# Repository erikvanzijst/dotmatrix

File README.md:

16x16 Monochrome Dot Matrix Display
===================================

A project to design and create a custom LED matrix display.

Full writeup and details at: https://medium.com/@erikvanzijst/custom-16x16-matrix-display-pcb-96c40290c8bc

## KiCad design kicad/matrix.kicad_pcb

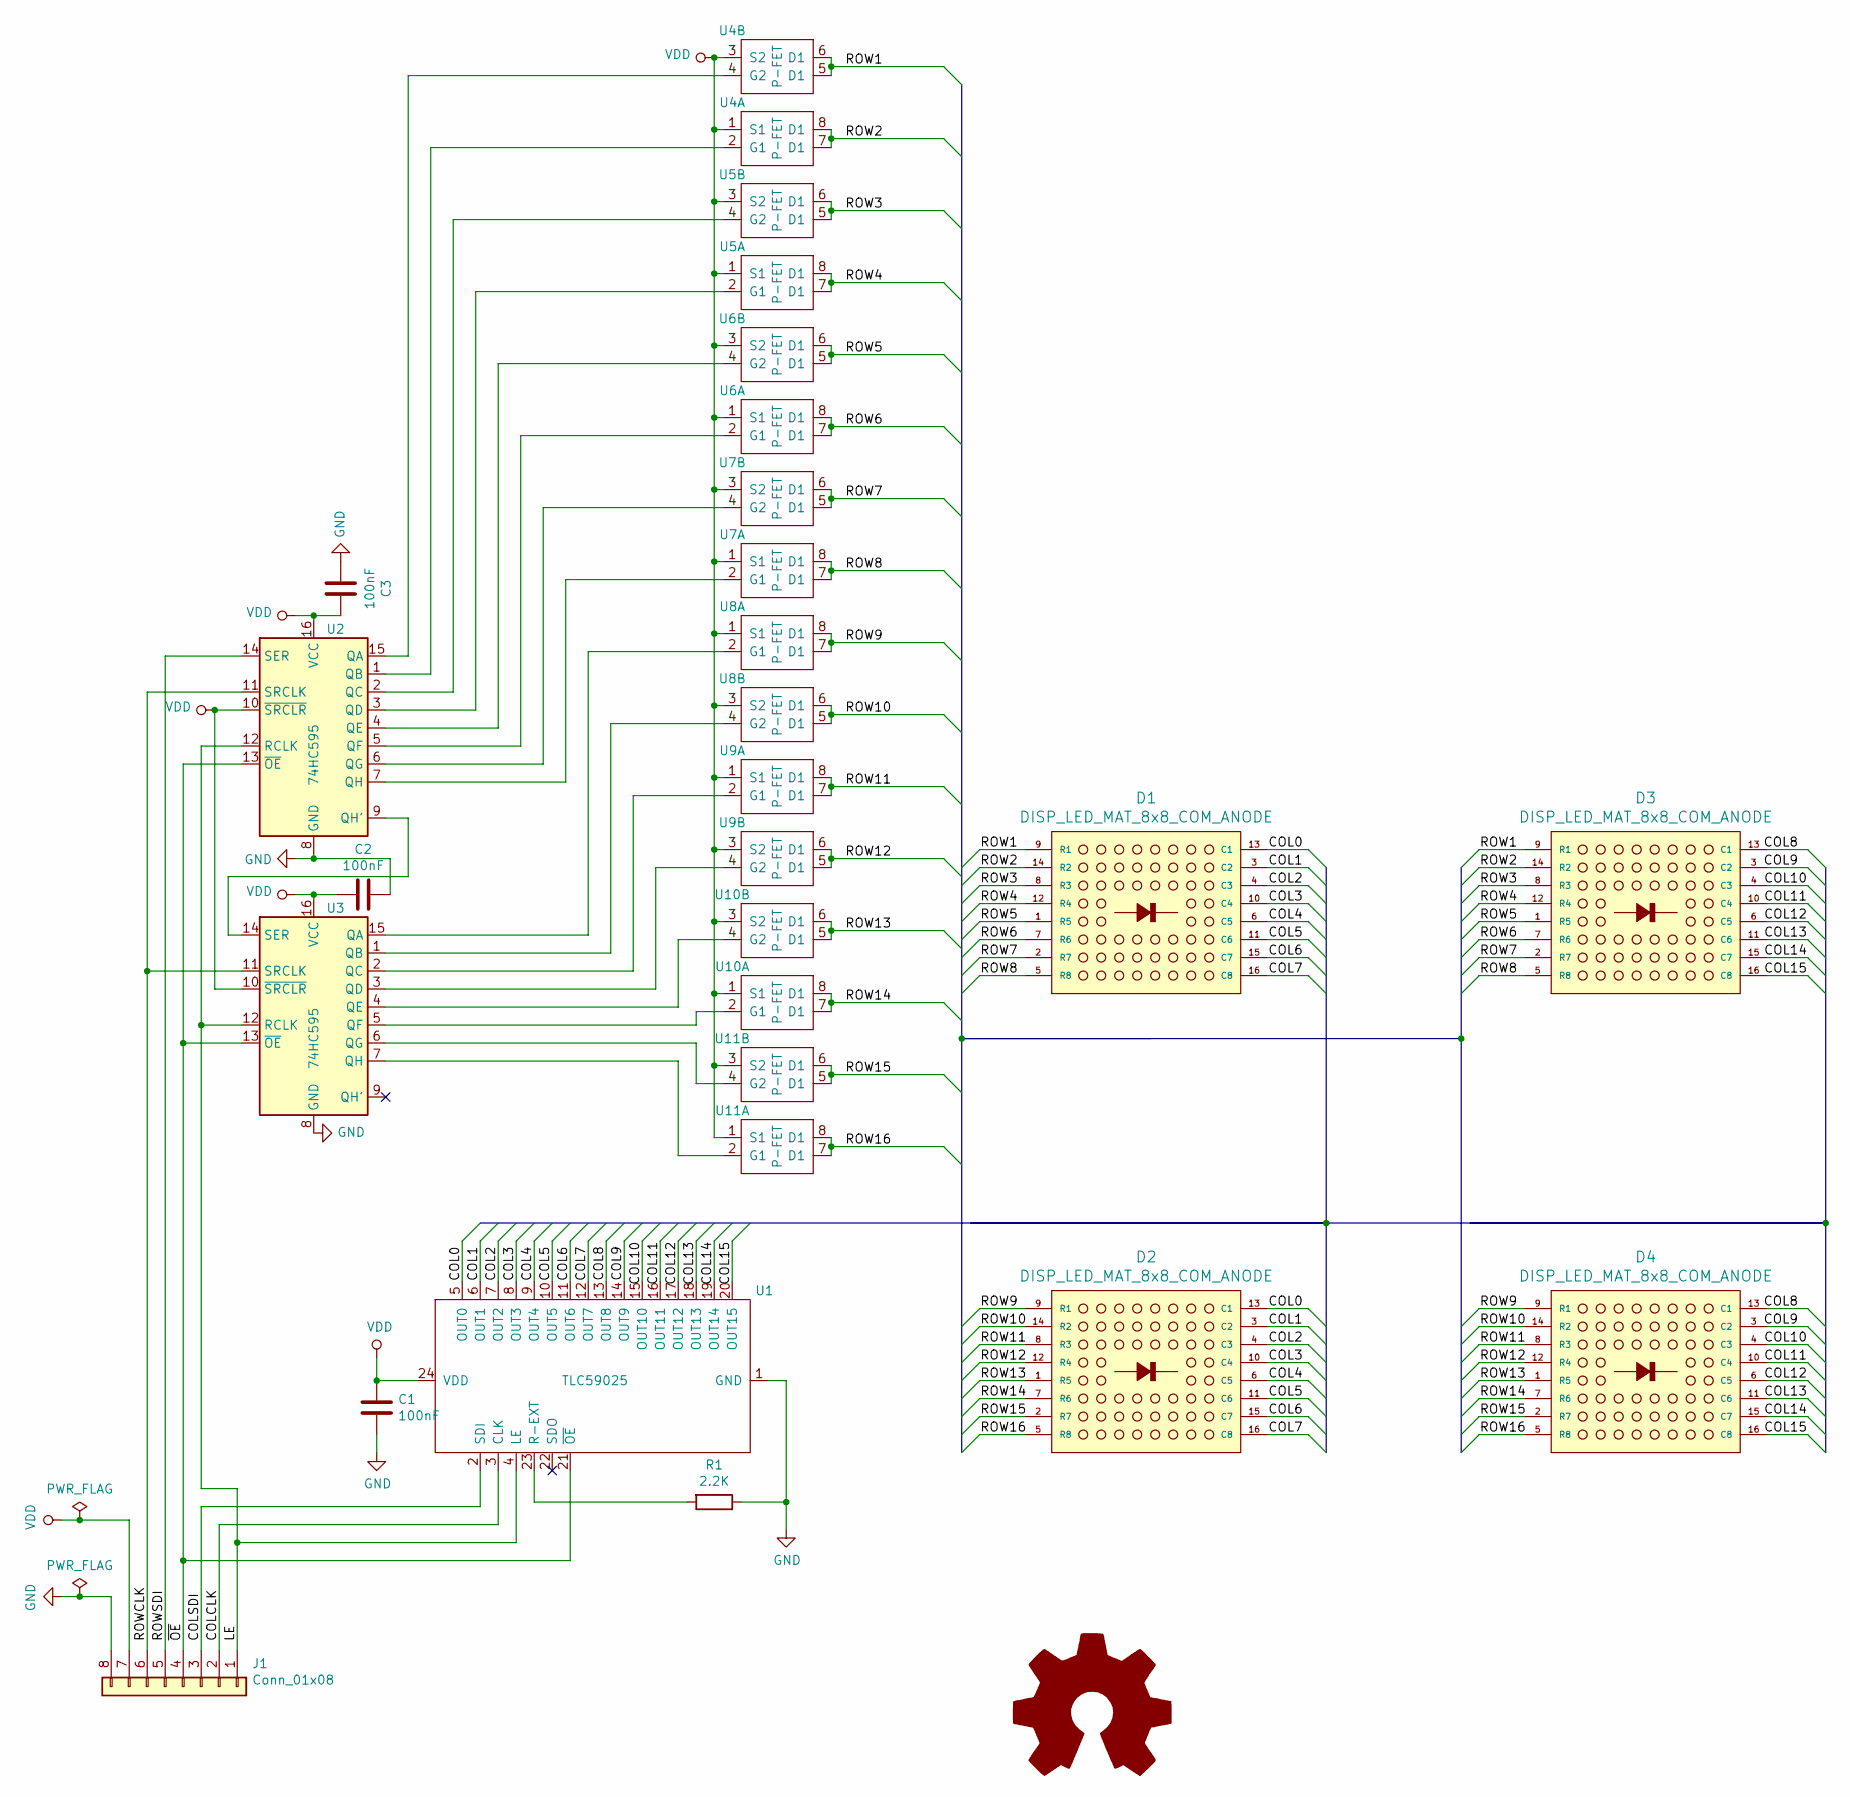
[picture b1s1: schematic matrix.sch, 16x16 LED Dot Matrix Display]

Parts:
C1, C2, C3: 100nF; C_0805_2012Metric_Pad1.15x1.40mm_widepads
D1, D2, D3, D4: DISP_LED_MAT_8x8_COM_ANODE; LED_8x8_3MM_38x38MM
J1: Conn_01x08; PinHeader_1x08_P2.54mm_Horizontal
R1: 2.2K; R_1206_3216Metric_Pad1.42x1.75mm_widepads
U1: TLC59025; SSOP-24_3.9x8.7mm_P0.635mm_widepads
U2, U3: 74HC595; SOIC-16_3.9x9.9mm_P1.27mm_widepads
U4, U5, U6, U7, U8, U9, U10, U11: P-FET; SOIC-8_3.9x4.9mm_P1.27mm_widepads

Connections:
/COL0: D1.13 (C1), D2.13 (C1), U1.5 (OUT0)
/COL1: D1.3 (C2), D2.3 (C2), U1.6 (OUT1)
/COL2: D1.4 (C3), D2.4 (C3), U1.7 (OUT2)
/COL3: D1.10 (C4), D2.10 (C4), U1.8 (OUT3)
/COL4: D1.6 (C5), D2.6 (C5), U1.9 (OUT4)
/COL5: D1.11 (C6), D2.11 (C6), U1.10 (OUT5)
/COL6: D1.15 (C7), D2.15 (C7), U1.11 (OUT6)
/COL7: D1.16 (C8), D2.16 (C8), U1.12 (OUT7)
/COL8: D3.13 (C1), D4.13 (C1), U1.13 (OUT8)
/COL9: D3.3 (C2), D4.3 (C2), U1.14 (OUT9)
/COL10: D3.4 (C3), D4.4 (C3), U1.15 (OUT10)
/COL11: D3.10 (C4), D4.10 (C4), U1.16 (OUT11)
/COL12: D3.6 (C5), D4.6 (C5), U1.17 (OUT12)
/COL13: D3.11 (C6), D4.11 (C6), U1.18 (OUT13)
/COL14: D3.15 (C7), D4.15 (C7), U1.19 (OUT14)
/COL15: D3.16 (C8), D4.16 (C8), U1.20 (OUT15)
/COLCLK: J1.2, U1.3 (CLK)
/COLSDI: J1.3, U1.2 (SDI)
/LE: J1.1, U1.4 (LE), U2.12 (RCLK), U3.12 (RCLK)
/ROW1: D1.9 (R1), D3.9 (R1), U4.5 (D1), U4.6 (D1)
/ROW2: D1.14 (R2), D3.14 (R2), U4.7 (D1), U4.8 (D1)
/ROW3: D1.8 (R3), D3.8 (R3), U5.5 (D1), U5.6 (D1)
/ROW4: D1.12 (R4), D3.12 (R4), U5.7 (D1), U5.8 (D1)
/ROW5: D1.1 (R5), D3.1 (R5), U6.5 (D1), U6.6 (D1)
/ROW6: D1.7 (R6), D3.7 (R6), U6.7 (D1), U6.8 (D1)
/ROW7: D1.2 (R7), D3.2 (R7), U7.5 (D1), U7.6 (D1)
/ROW8: D1.5 (R8), D3.5 (R8), U7.7 (D1), U7.8 (D1)
/ROW9: D2.9 (R1), D4.9 (R1), U8.7 (D1), U8.8 (D1)
/ROW10: D2.14 (R2), D4.14 (R2), U8.5 (D1), U8.6 (D1)
/ROW11: D2.8 (R3), D4.8 (R3), U9.7 (D1), U9.8 (D1)
/ROW12: D2.12 (R4), D4.12 (R4), U9.5 (D1), U9.6 (D1)
/ROW13: D2.1 (R5), D4.1 (R5), U10.5 (D1), U10.6 (D1)
/ROW14: D2.7 (R6), D4.7 (R6), U10.7 (D1), U10.8 (D1)
/ROW15: D2.2 (R7), D4.2 (R7), U11.5 (D1), U11.6 (D1)
/ROW16: D2.5 (R8), D4.5 (R8), U11.7 (D1), U11.8 (D1)
/ROWCLK: J1.6, U2.11 (SRCLK), U3.11 (SRCLK)
/ROWSDI: J1.5, U2.14 (SER)
/~OE: J1.4, U1.21 (~OE), U2.13 (~OE), U3.13 (~OE)
GND: C1.2, C2.1, C3.2, J1.8, R1.1, U1.1 (GND), U2.8 (GND), U3.8 (GND)
unnamed: R1.2, U1.23 (R-EXT)
unnamed: U2.1 (QB), U4.2 (G1)
unnamed: U2.2 (QC), U5.4 (G2)
unnamed: U2.3 (QD), U5.2 (G1)
unnamed: U2.4 (QE), U6.4 (G2)
unnamed: U2.5 (QF), U6.2 (G1)
unnamed: U2.6 (QG), U7.4 (G2)
unnamed: U2.7 (QH), U7.2 (G1)
unnamed: U2.9 (QH'), U3.14 (SER)
unnamed: U2.15 (QA), U4.4 (G2)
unnamed: U3.1 (QB), U8.4 (G2)
unnamed: U3.2 (QC), U9.2 (G1)
unnamed: U3.3 (QD), U9.4 (G2)
unnamed: U3.15 (QA), U8.2 (G1)
unnamed: U3.5 (QF), U10.2 (G1)
unnamed: U3.4 (QE), U10.4 (G2)
unnamed: U3.7 (QH), U11.2 (G1)
unnamed: U3.6 (QG), U11.4 (G2)
VDD: C1.1, C2.2, C3.1, J1.7, U1.24 (VDD), U2.10 (~SRCLR), U2.16 (VCC), U3.10 (~SRCLR), U3.16 (VCC), U4.1 (S1), U4.3 (S2), U5.1 (S1), U5.3 (S2), U6.1 (S1), U6.3 (S2), U7.1 (S1), U7.3 (S2), U8.1 (S1), U8.3 (S2), U9.1 (S1), U9.3 (S2), U10.1 (S1), U10.3 (S2), U11.1 (S1), U11.3 (S2)

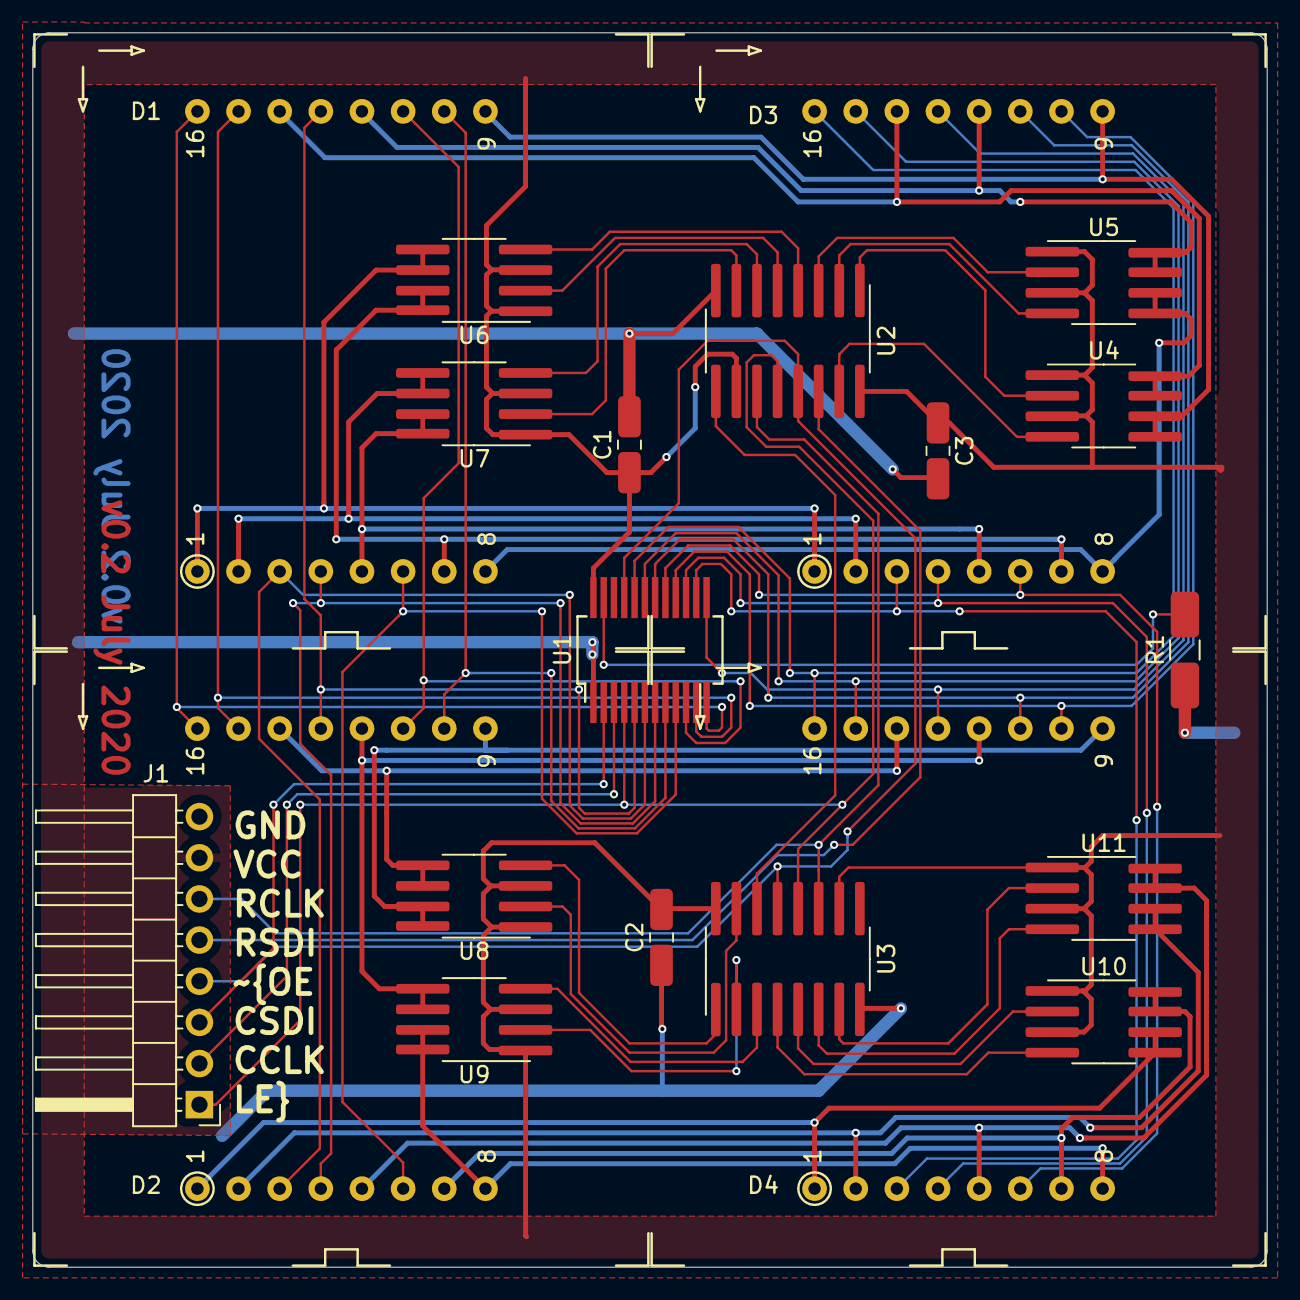
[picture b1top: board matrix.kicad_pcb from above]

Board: 2 copper layers, 76.2 x 76.2 mm, 20 parts (0 on the bottom side), 58 nets.

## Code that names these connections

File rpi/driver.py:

from ctypes import c_bool, c_uint16
from time import time
from multiprocessing import Process, Value, Array
from typing import List

from gpiozero import DigitalOutputDevice


def _pulse(dev: DigitalOutputDevice) -> None:
    dev.pin.state = False
    dev.pin.state = True


def _run(screen: Array, die: Value, rowclk: int, rowsdi: int, oe: int, colsdi: int, colclk: int, le: int,
         showhz: bool):
    print("Connecting to display...")
    ROWSDI = DigitalOutputDevice(rowsdi)
    ROWCLK = DigitalOutputDevice(rowclk)
    COLSDI = DigitalOutputDevice(colsdi)
    COLCLK = DigitalOutputDevice(colclk)
    OE = DigitalOutputDevice(oe, initial_value=True)
    LE = DigitalOutputDevice(le)

    try:
        OE.pin.state = False
        cnt, last = 0, time()
        width = 2 ** MatrixDriver.DIM

        while not die.value:
            for row in range(MatrixDriver.DIM):
                LE.pin.state = False
                ROWSDI.pin.state = row != 0
                _pulse(ROWCLK)

                bit = 1
                value = screen[row]
                while bit < width:
                    COLSDI.pin.state = bool(value & bit)
                    _pulse(COLCLK)
                    bit <<= 1
                _pulse(LE)

            if showhz:
                cnt += 1
                now = time()
                if now - last > .5:
                    print("Refresh rate: %.1fHz" % (cnt / (now - last)))
                    cnt, last = 0, now
    finally:
        print("Releasing display...")
        ROWSDI.close()
        ROWCLK.close()
        COLSDI.close()
        COLCLK.close()
        LE.close()
        OE.close()


class MatrixDriver(object):
    DIM = 16

    def __init__(self, rowclk: int = 2, rowsdi: int = 3, oe: int = 4, colsdi: int = 17, colclk: int = 27, le: int = 22,
                 showhz: bool = False) -> None:
        self.screen = Array(c_uint16, [0] * self.DIM, lock=True)
        self.die = Value(c_bool, False)

        self.showhz = showhz
        self.process = Process(target=_run,
                               args=(self.screen, self.die, rowclk, rowsdi, oe, colsdi, colclk, le, showhz))
        self.process.start()

    def draw(self, screen: List[int]) -> None:
        assert len(screen) == self.DIM
        for i in range(self.DIM):
            self.screen[i] = screen[i]

    def setpixel(self, row: int, col: int, on: bool) -> None:
        if on:
            self.screen[row] |= (1 << col)
        else:
            self.screen[row] &= ((1 << col) ^ 0xff)

    def close(self) -> None:
        self.die.value = True
        self.process.join()

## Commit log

2020-06-01 Initial schematic for dot matrix display
2020-06-02 Add footprints and initial layout
2020-06-06 Add headers to schematic
2020-06-07 Add headers to PCB layout
2020-06-07 Add datasheets and long pad footprints
2020-06-07 Enlarge display footprint and SMD pad widths
2020-06-07 OshPark design rules and copper GND pour
2020-06-07 Wire up cathodes
2020-06-07 Switch to P-channel FETs in SOIC-8 package
2020-06-07 Add power net
2020-06-08 Finished most of the layout
2020-06-10 Scaled up 3d display models
    Also wired up the remaining nets.
2020-06-10 Updated widened display footprint
    Still needs layout adjustments to adapt to the larger footprint and
    moved pin locations.
2020-06-11 Resize board and place components
    Routing up next.
2020-06-11 Widen capacitor footprint pads
    Easier for hand soldering.
2020-06-11 Widen resistor pads
    For easier hand soldering.
2020-06-11 Power net in place
2020-06-11 Wire up LED cathodes
2020-06-14 Wire up most of the layout
2020-06-14 Wire up everything but ground net
2020-06-14 Wire up remaining traces
2020-06-14 Add Open Hardware and KiCad logos
2020-06-15 Added header datasheets
2020-06-15 Generate Gerbers
2020-06-15 Add README and renders
2020-06-22 Add testing code
    Added a Python, gpiozero-based testing program for Raspberry Pi to
    display test patterns on the matrix display.
2020-06-22 Add ctrl-c handling
2020-07-03 Assign gpio pint numbers
2020-07-03 Fix MOSFET symbol pinout
    This fixes the mistake in the MOSFET symbol that incorrectly paired
    up input pins 1-2 with output pins 5-6 and input 3-4 with 7-8.
    Instead, pins 1-2 (source & gate) map to output pins 7-8 (drain) and
    3-4 map to 5-6.
    The result of this mistake in v01 of the board means that every pair
    of display rows are flipped. At a high refresh rate this should not
2020-07-03 Add Python requirements for Raspberry Pi code
2020-07-04 Add Arduino firmware
    This adds an Arduino project to drive the display. It uses a timer
    interrupt to refresh the screen at 61Hz while the main loop is
    available for code.
2020-07-04 Cleanup Arduino firmware
2020-07-04 Move row adjustment out of interrupt routine
2020-07-05 Tetris: Add tetromino definitions
    Also implemented basic falling movement and colliding with the
    bottom.
2020-07-06 Tetris: Add buttons
2020-07-06 Tetris: Remove completed lines
2020-07-06 Tetris: Fix incorrect J tetromino
2020-07-06 Tetris: Add press-and-hold for down button
2020-07-06 Tetris: Un-mirror screen and board buffers
2020-07-06 Tetris: Rename struct member
2020-07-06 Tetris: Narrow field to 10 width
    The official Tetris game has a field that is 10x20 and so narrow our
    field to 10 pixels wide. This leaves some room on the side to show
    the upcoming Tetromino.
    Unfortunately our display is only 16 pixels high, but what can you
    do.
2020-07-06 Tetris: Add preview in side bar
2020-07-06 Document MOSFET layout fail
2020-07-06 Tetris: Increase speed with score
    Very basic scoring mechanism based on number of lines cleared.
    Speed is linearly related to score.
2020-07-06 Tetris: Added image of Adruino setup
2020-07-08 Tetris: Fix bug in copying board to screen
    Also increased soft-drop speed and lowered global memory usage.
2020-07-12 Add text scrolling and basic character set
2020-07-12 Tetris: debug cleanup
2020-07-12 Tetris: Implement original BPS scoring
2020-07-12 Tetris: Tolerate lowercase text
2020-07-12 Added photos
2020-07-12 Tetris: Add MIT license
2020-07-15 Increase refresh rate to 125Hz
2020-07-15 Add PulseView logic analyzer screenshots
2020-07-17 Add final photos and link to Medium post
2020-07-18 Tetris: Store hiscore in EEPROM
2020-07-18 Tetris: Show current + hiscore at end screen
2020-07-19 Tetris: Use FastGPIO for 10x faster screen IO
2020-07-26 Tetris: Add pause button
2022-01-21 Bump ipython from 7.15.0 to 7.16.3 in /rpi
    Bumps [ipython](https://github.com/ipython/ipython) from 7.15.0 to 7.16.3.
    - [Release notes](https://github.com/ipython/ipython/releases)
    - [Commits](https://github.com/ipython/ipython/compare/7.15.0...7.16.3)
    ---
    updated-dependencies:
    - dependency-name: ipython
2023-02-10 Bump ipython from 7.16.3 to 8.10.0 in /rpi
    Bumps [ipython](https://github.com/ipython/ipython) from 7.16.3 to 8.10.0.
    - [Release notes](https://github.com/ipython/ipython/releases)
    - [Commits](https://github.com/ipython/ipython/compare/7.16.3...8.10.0)
    ---
    updated-dependencies:
    - dependency-name: ipython
